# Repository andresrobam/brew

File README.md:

# brew

Raspberry Pi based brewing controller.\
Written for and tested on a Raspberry Pi 4B running DietPi 9.9, but might work on other combinations.\
Requires docker and docker compose to be installed.
Runs on http://localhost:80. Port can be changed in the `docker-compose` file.

PID logic copied from [hirschmann/pid-autotune](https://github.com/hirschmann/pid-autotune).

## Issues

Fan tachometer signal reading does not work as intended and is hidden in the UI. Will be fixed in a future revision. \
Transistor footprints on the PCB have their pads very close together which makes soldering difficult. Will be changed for wider footprint in a future revision.

## GPIO pins

- GPIO04 (board 7) - Data channel of a DS18B20 temperature sensor (input)
- GPIO12 (board 32) - Fan PWM (output)
- GPIO13 (board 33) - PWM signal to drive the heater through a solid state relay (output)
- GPIO24 (board 18) - Buzzer (output)
- GPIO26 (board 37) - Fan tachometer signal (input)
- GPIO27 (board 13) - Pump relay control (output)

More details about the connections (necessary components and wiring) can be found in the `electronics` sub-directory (open with KiCad).

## Configuring temperature sensor and PWM modules

Add hardware PWM to boot configuration:

```
sudo echo -e "\ndtoverlay=pwm-2chan,pin=12,func=4,pin2=13,func2=4\n" >> /boot/config.txt
```

Add 1-Wire to boot configuration:

```
sudo echo -e "\ndtoverlay=w1-gpio\n" >> /boot/config.txt
```

Reboot:

```
sudo reboot
```

Add modules:

```
sudo modprobe w1-gpio
sudo modprobe w1-therm
```

## Installation

Configure DS18B20 if not alread configured (see previous section).

Install gcc:
```
apt install gcc
```

Navigate to the folder you want to install this application to and clone the repository:
```
git clone https://github.com/andresrobam/brew.git
```

Start the UI:
```
docker compose up -d
```

Navigate to the backend directory, install requirements and start the backend:
```
cd server
pip3 install -r requirements.txt
python3 app.py
```

## Local build

To build and run locally:

```
docker compose -f docker-compose-local.yml up -d
```

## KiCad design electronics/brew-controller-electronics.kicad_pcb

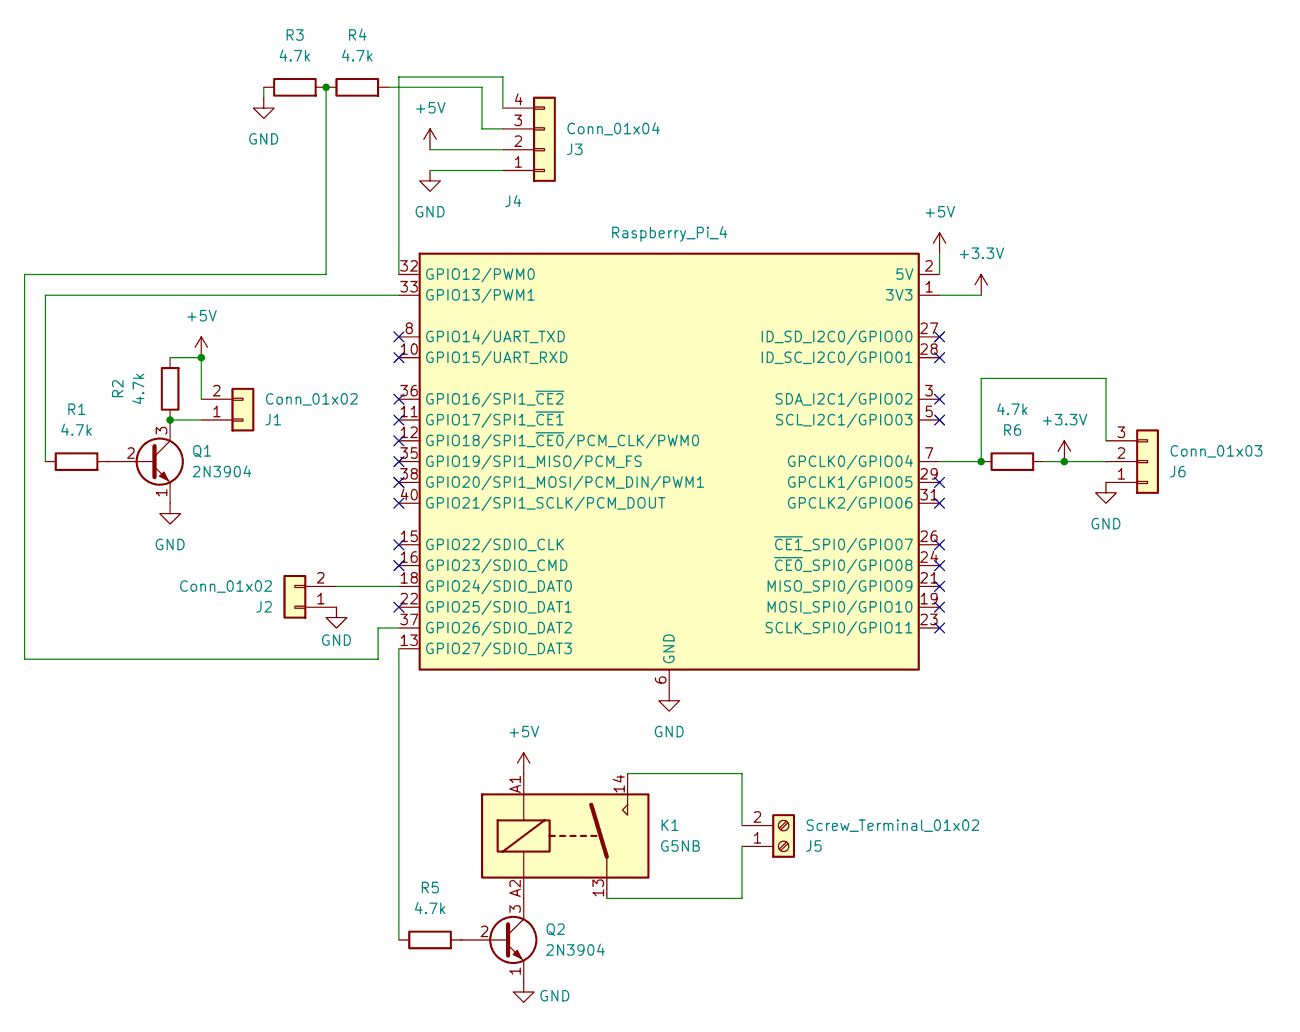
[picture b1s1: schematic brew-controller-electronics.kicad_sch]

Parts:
J1, J2: Conn_01x02; PinSocket_1x02_P2.54mm_Vertical
J3: Conn_01x04; PinSocket_1x04_P2.54mm_Vertical
J4: Raspberry_Pi_4; PinHeader_2x20_P2.54mm_Vertical
J5: Screw_Terminal_01x02; TerminalBlock_RND_205-00287_1x02_P5.08mm_Horizontal
J6: Conn_01x03; PinHeader_1x03_P2.54mm_Vertical
K1: G5NB; Relay_SPST_Omron_G5NB
Q1, Q2: 2N3904; TO-92_Inline
R1, R2, R3, R4, R5, R6: 4.7k; R_Axial_DIN0207_L6.3mm_D2.5mm_P10.16mm_Horizontal

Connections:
+3.3V: J4.1 (3V3), J4.17 (3V3), J6.2, R6.2
+5V: J1.2, J3.2, J4.2 (5V), J4.4 (5V), K1.A1, R2.2
GND: J2.1, J3.1, J4.6 (GND), J4.9 (GND), J4.14 (GND), J4.20 (GND), J4.25 (GND), J4.30 (GND), J4.34 (GND), J4.39 (GND), J6.1, Q1.1 (E), Q2.1 (E), R3.1
unnamed: J1.1, Q1.3 (C), R2.1
unnamed: J2.2, J4.18 (GPIO24/SDIO_DAT0)
unnamed: J3.3, R4.2
unnamed: J3.4, J4.32 (GPIO12/PWM0)
unnamed: J4.7 (GPCLK0/GPIO04), J6.3, R6.1
unnamed: J4.33 (GPIO13/PWM1), R1.1
unnamed: J4.37 (GPIO26/SDIO_DAT2), R3.2, R4.1
unnamed: J4.13 (GPIO27/SDIO_DAT3), R5.1
unnamed: J5.1, K1.13
unnamed: J5.2, K1.14
unnamed: Q1.2 (B), R1.2
unnamed: Q2.2 (B), R5.2
unnamed: K1.A2, Q2.3 (C)

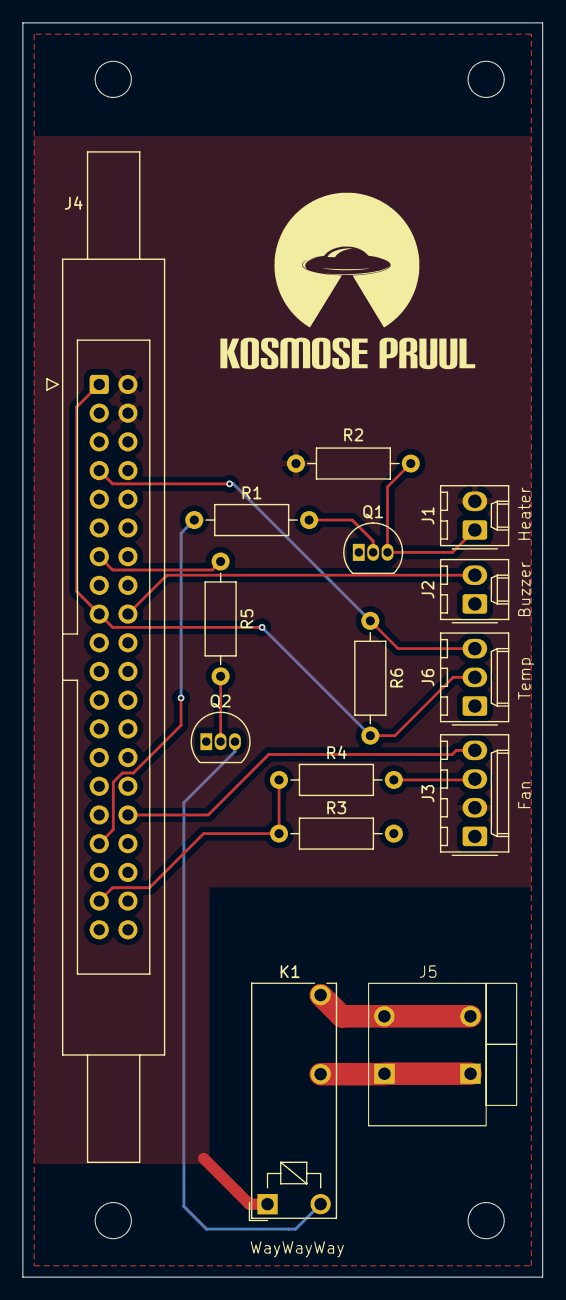
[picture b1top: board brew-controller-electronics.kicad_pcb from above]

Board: 2 copper layers, 46.0 x 111.0 mm, 15 parts (0 on the bottom side), 16 nets.

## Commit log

2025-02-07 Initial commits.
2025-02-07 Change file format.
2025-02-07 Add trigger.
2025-02-07 Fix workflow.
2025-02-07 Add uses.
2025-02-07 Add more ignores.
2025-02-07 Add gitignores.
2025-02-07 Add nginx conf.
2025-02-07 Add backend server proxy.
2025-02-07 Fix dockers.
2025-02-07 Fix docker.
2025-02-07 Multi-arch builds.
2025-02-07 Add info to readme.
2025-02-07 Ignore lock files.
2025-02-07 Multi arch builds.
2025-02-07 Improve readme.
2025-02-08 Use gunicorn, configure logging.
2025-02-09 Create LICENSE
2025-02-10 UI improvements.
2025-02-13 Improvements.
2025-02-13 Ignore a11y.
2025-02-13 Add content to info screen.
2025-02-13 Add fan RPM
2025-02-16 Disable forward/backward gestures.
2025-02-23 Temperature reading logic.
2025-02-23 Add GPIO, IP address, remove backend docker.
2025-02-23 Fix typo.
2025-02-23 Better readme.
2025-02-23 Run with host networking.
2025-02-23 Readme fixes, buzzer.
2025-02-23 Increase buzzer time.
2025-02-23 use async/await
2025-02-23 Fix async/await
2025-02-23 Use hardware PWM for fan and heater.
2025-02-23 Change config location.
2025-02-23 Remove TODO
2025-02-23 Add fan rpm logic
2025-02-23 Remove interrupt debounce.
2025-02-23 Use pull-down resistor for tach and rising edge for interrupt.
2025-02-23 Add debug print.
2025-02-23 Revert changes.
2025-02-23 Disable pull-up resistor.
2025-02-23 Hide tachometer signal, improve readme.
2025-04-13 Autotune fixes
2025-04-13 Fix typo
2025-04-13 Fix autotune
2025-04-13 Round temperature
2025-04-13 Fix autotune messages
2025-04-13 Change autotune step amount
2025-04-13 Add peak count log
2025-05-04 Fix temperature reading when >= 100C
2025-05-04 Reverse log output
2025-05-04 Detect time shift and empty charts
2025-05-04 Format temperature and duty cycle values
2025-05-04 Disable edge detection
